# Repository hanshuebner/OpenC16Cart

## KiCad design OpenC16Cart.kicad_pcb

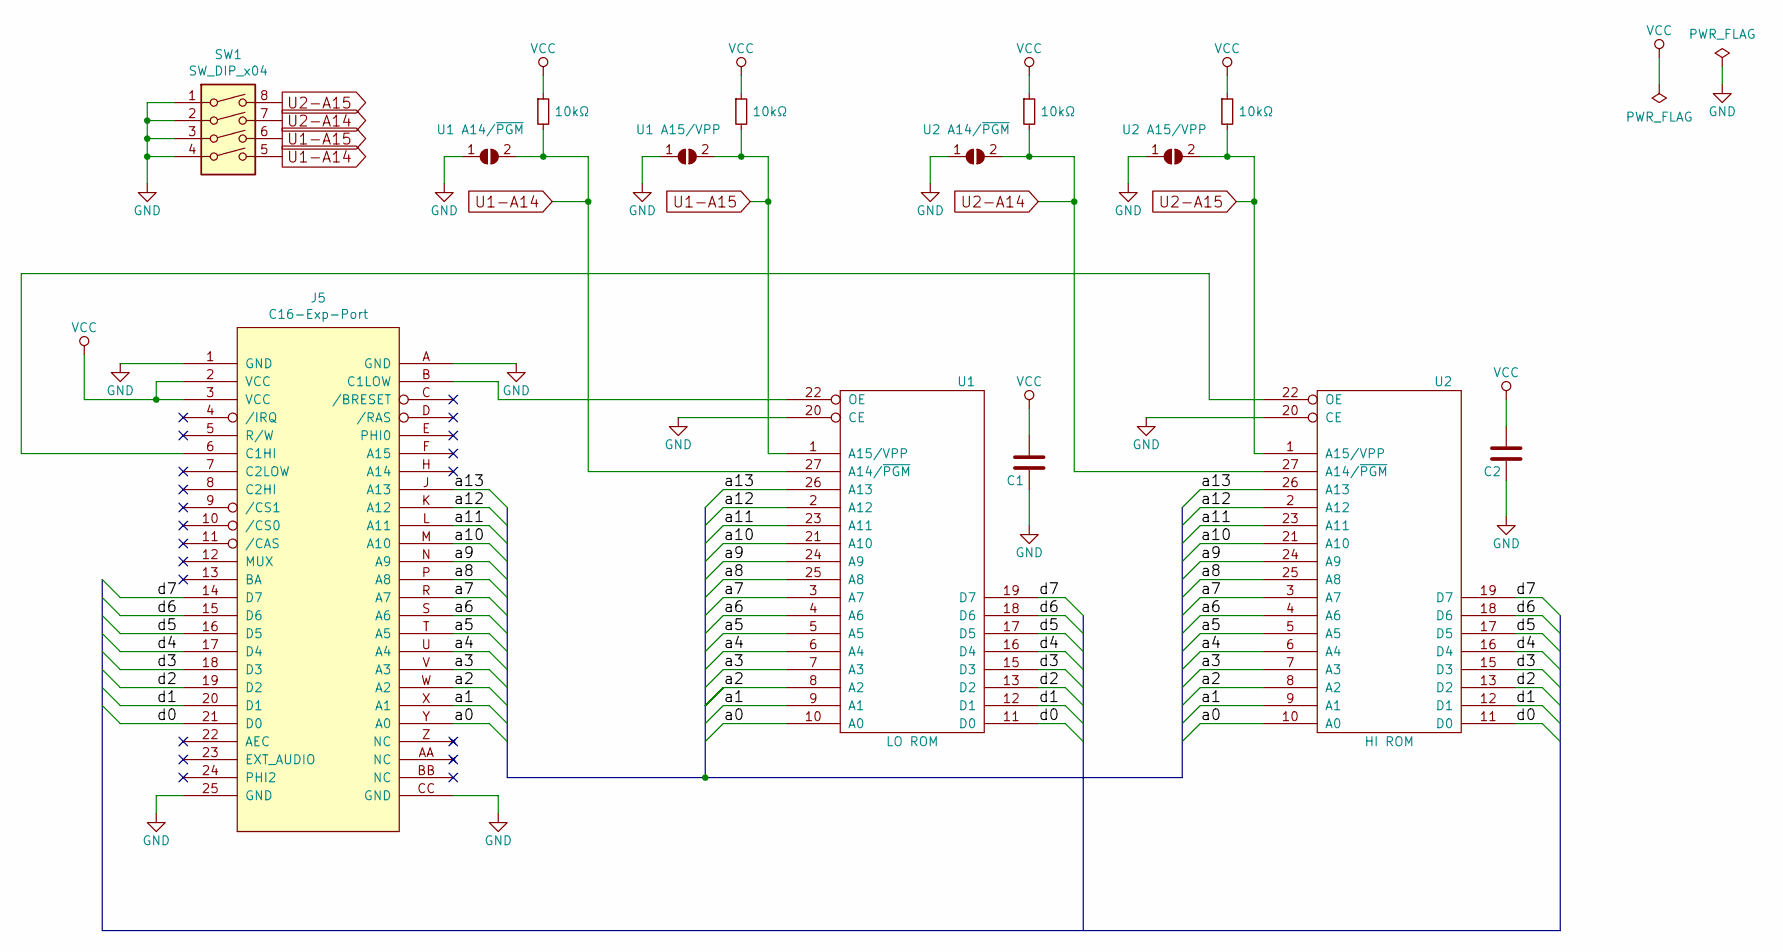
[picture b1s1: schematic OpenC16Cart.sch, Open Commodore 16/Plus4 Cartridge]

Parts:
C1, C2: C; C_0805_HandSoldering
J5: C16-Exp-Port; C16_Cart_Conn
JP1: U1 A14/~PGM; SolderJumper-2_P1.3mm_Open_RoundedPad1.0x1.5mm
JP2: U1 A15/VPP; SolderJumper-2_P1.3mm_Open_RoundedPad1.0x1.5mm
JP3: U2 A14/~PGM; SolderJumper-2_P1.3mm_Open_RoundedPad1.0x1.5mm
JP4: U2 A15/VPP; SolderJumper-2_P1.3mm_Open_RoundedPad1.0x1.5mm
R1, R2, R3, R4: 10kΩ; R_0805_2012Metric_Pad1.15x1.40mm_HandSolder
SW1: SW_DIP_x04; SW_DIP_SPSTx04_Piano_10.8x11.72mm_W7.62mm_P2.54mm
U1: LO ROM; dil_28-600_socket_ThinSilkS
U2: HI ROM; dil_28-600_socket_ThinSilkS

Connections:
/a0: J5.Y (A0), U1.10 (A0), U2.10 (A0)
/a1: J5.X (A1), U1.9 (A1), U2.9 (A1)
/a2: J5.W (A2), U1.8 (A2), U2.8 (A2)
/a3: J5.V (A3), U1.7 (A3), U2.7 (A3)
/a4: J5.U (A4), U1.6 (A4), U2.6 (A4)
/a5: J5.T (A5), U1.5 (A5), U2.5 (A5)
/a6: J5.S (A6), U1.4 (A6), U2.4 (A6)
/a7: J5.R (A7), U1.3 (A7), U2.3 (A7)
/a8: J5.P (A8), U1.25 (A8), U2.25 (A8)
/a9: J5.N (A9), U1.24 (A9), U2.24 (A9)
/a10: J5.M (A10), U1.21 (A10), U2.21 (A10)
/a11: J5.L (A11), U1.23 (A11), U2.23 (A11)
/a12: J5.K (A12), U1.2 (A12), U2.2 (A12)
/a13: J5.J (A13), U1.26 (A13), U2.26 (A13)
/d0: J5.21 (D0), U1.11 (D0), U2.11 (D0)
/d1: J5.20 (D1), U1.12 (D1), U2.12 (D1)
/d2: J5.19 (D2), U1.13 (D2), U2.13 (D2)
/d3: J5.18 (D3), U1.15 (D3), U2.15 (D3)
/d4: J5.17 (D4), U1.16 (D4), U2.16 (D4)
/d5: J5.16 (D5), U1.17 (D5), U2.17 (D5)
/d6: J5.15 (D6), U1.18 (D6), U2.18 (D6)
/d7: J5.14 (D7), U1.19 (D7), U2.19 (D7)
GND: C1.1, C2.1, J5.1 (GND), J5.25 (GND), J5.A (GND), J5.CC (GND), JP1.1 (A), JP2.1 (A), JP3.1 (A), JP4.1 (A), SW1.1, SW1.2, SW1.3, SW1.4, U1.14 (GND), U1.20 (CE), U2.14 (GND), U2.20 (CE)
unnamed: J5.6 (C1HI), U2.22 (OE)
unnamed: J5.B (C1LOW), U1.22 (OE)
U1-A14: JP1.2 (B), R1.2, SW1.5, U1.27 (A14/~PGM)
U1-A15: JP2.2 (B), R2.2, SW1.6, U1.1 (A15/VPP)
U2-A14: JP3.2 (B), R3.2, SW1.7, U2.27 (A14/~PGM)
U2-A15: JP4.2 (B), R4.2, SW1.8, U2.1 (A15/VPP)
VCC: C1.2, C2.2, J5.2 (VCC), J5.3 (VCC), R1.1, R2.1, R3.1, R4.1, U1.28 (VCC), U2.28 (VCC)

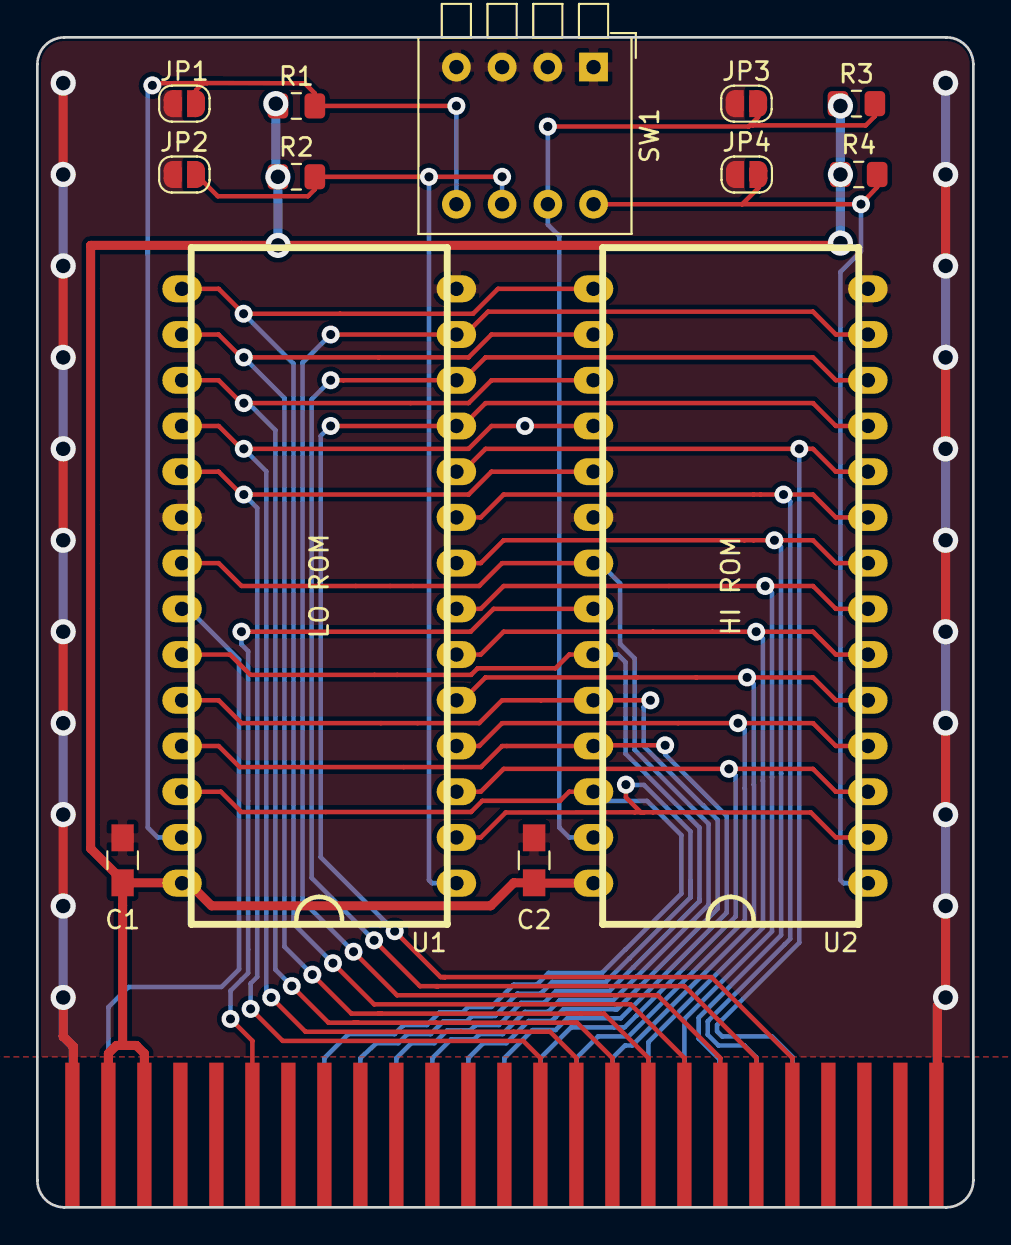
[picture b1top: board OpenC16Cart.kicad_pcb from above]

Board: 2 copper layers, 52.0 x 65.0 mm, 14 parts (0 on the bottom side), 30 nets.

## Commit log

2020-07-12 Layout redone, schematics simplified
2020-07-12 Generate production gerbers
